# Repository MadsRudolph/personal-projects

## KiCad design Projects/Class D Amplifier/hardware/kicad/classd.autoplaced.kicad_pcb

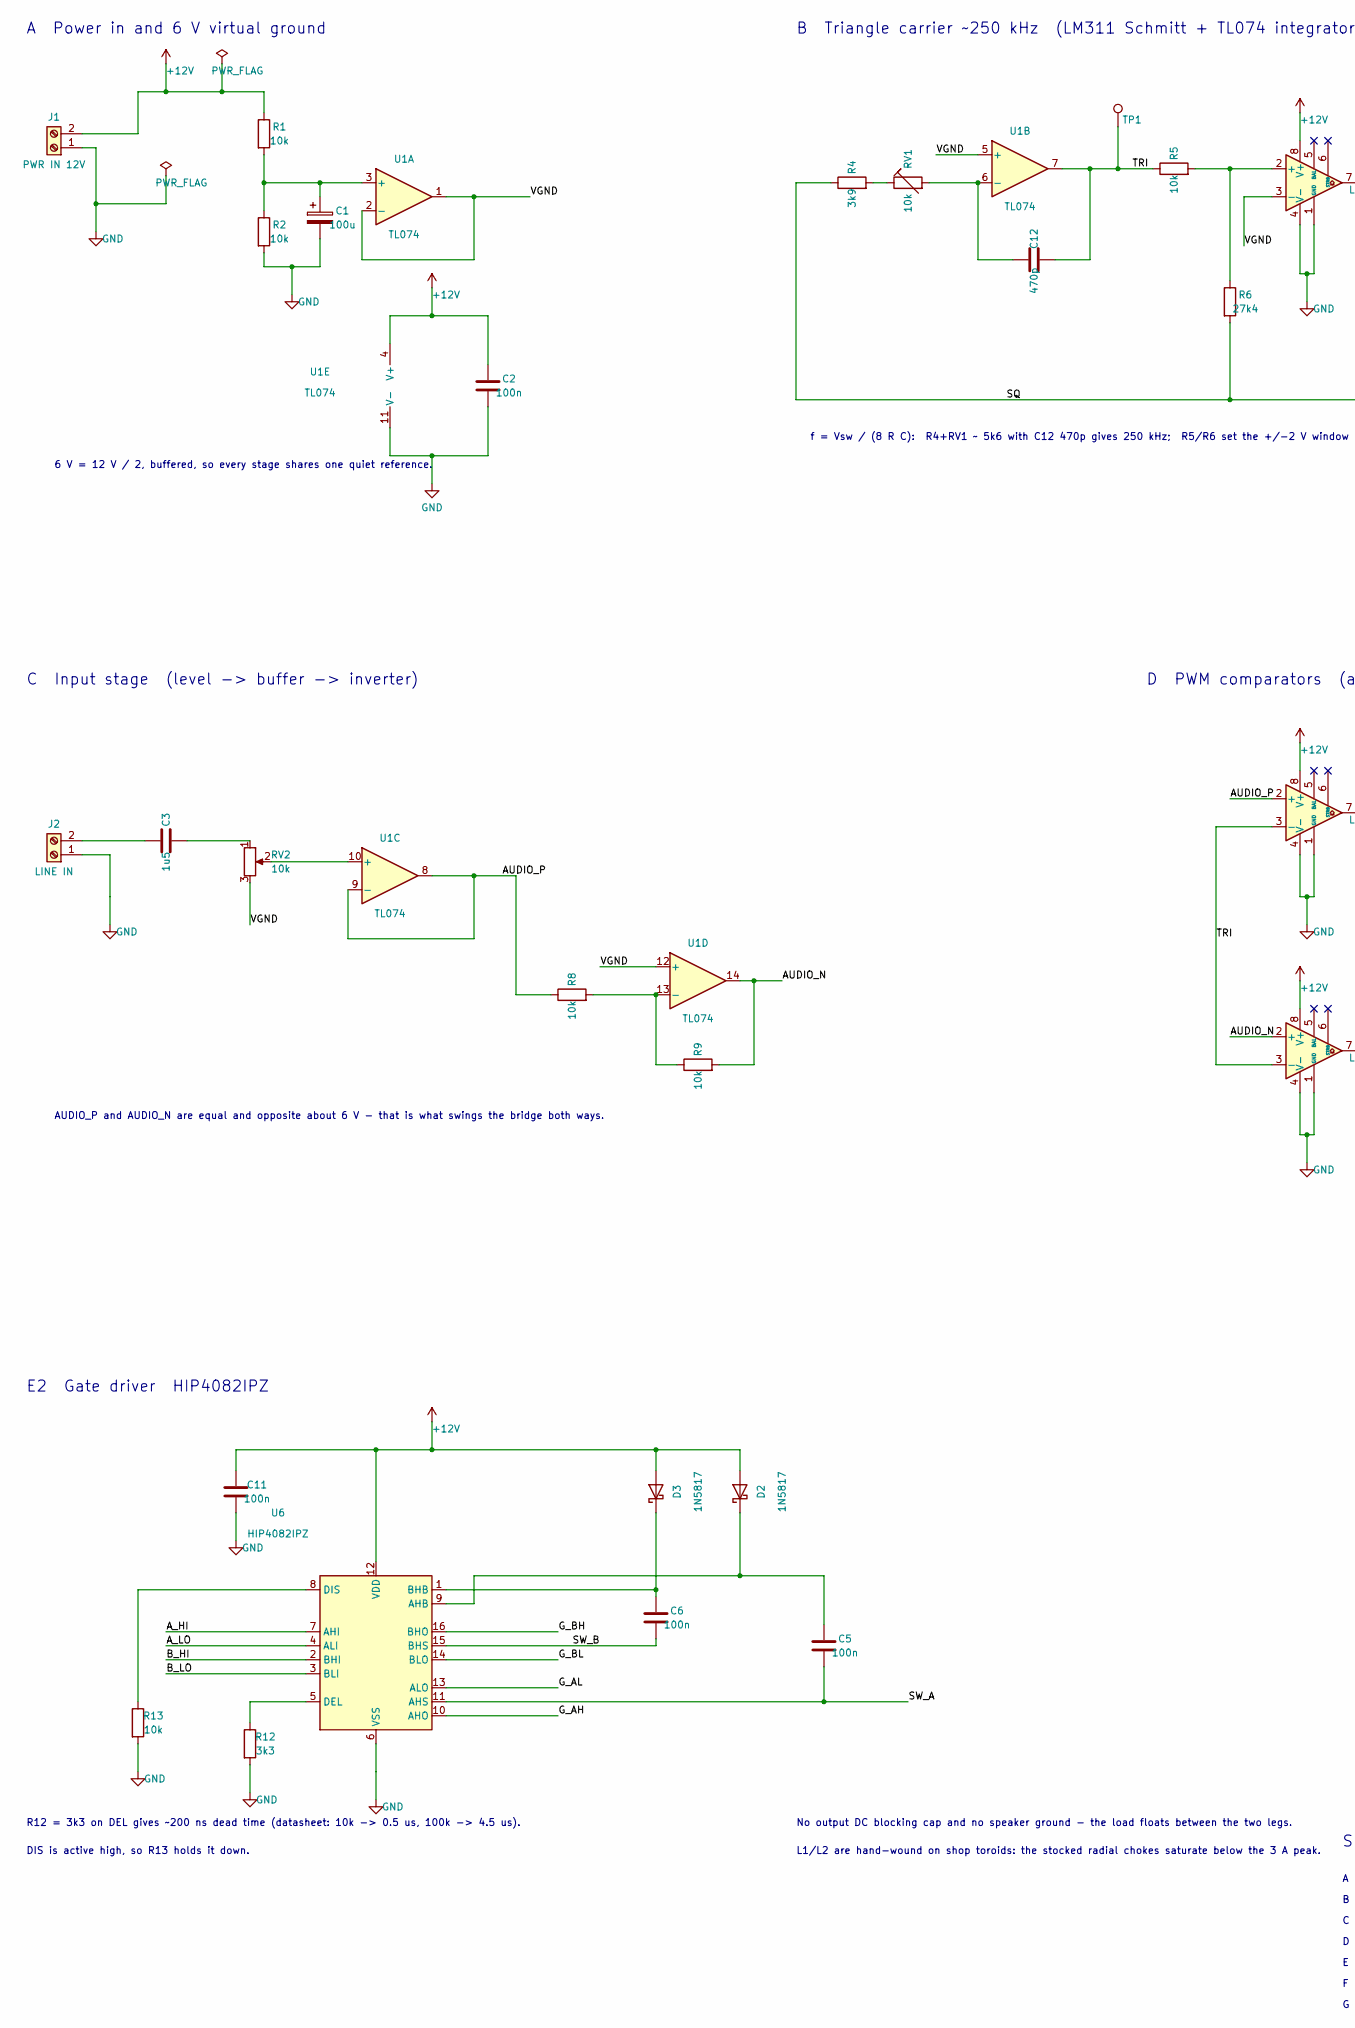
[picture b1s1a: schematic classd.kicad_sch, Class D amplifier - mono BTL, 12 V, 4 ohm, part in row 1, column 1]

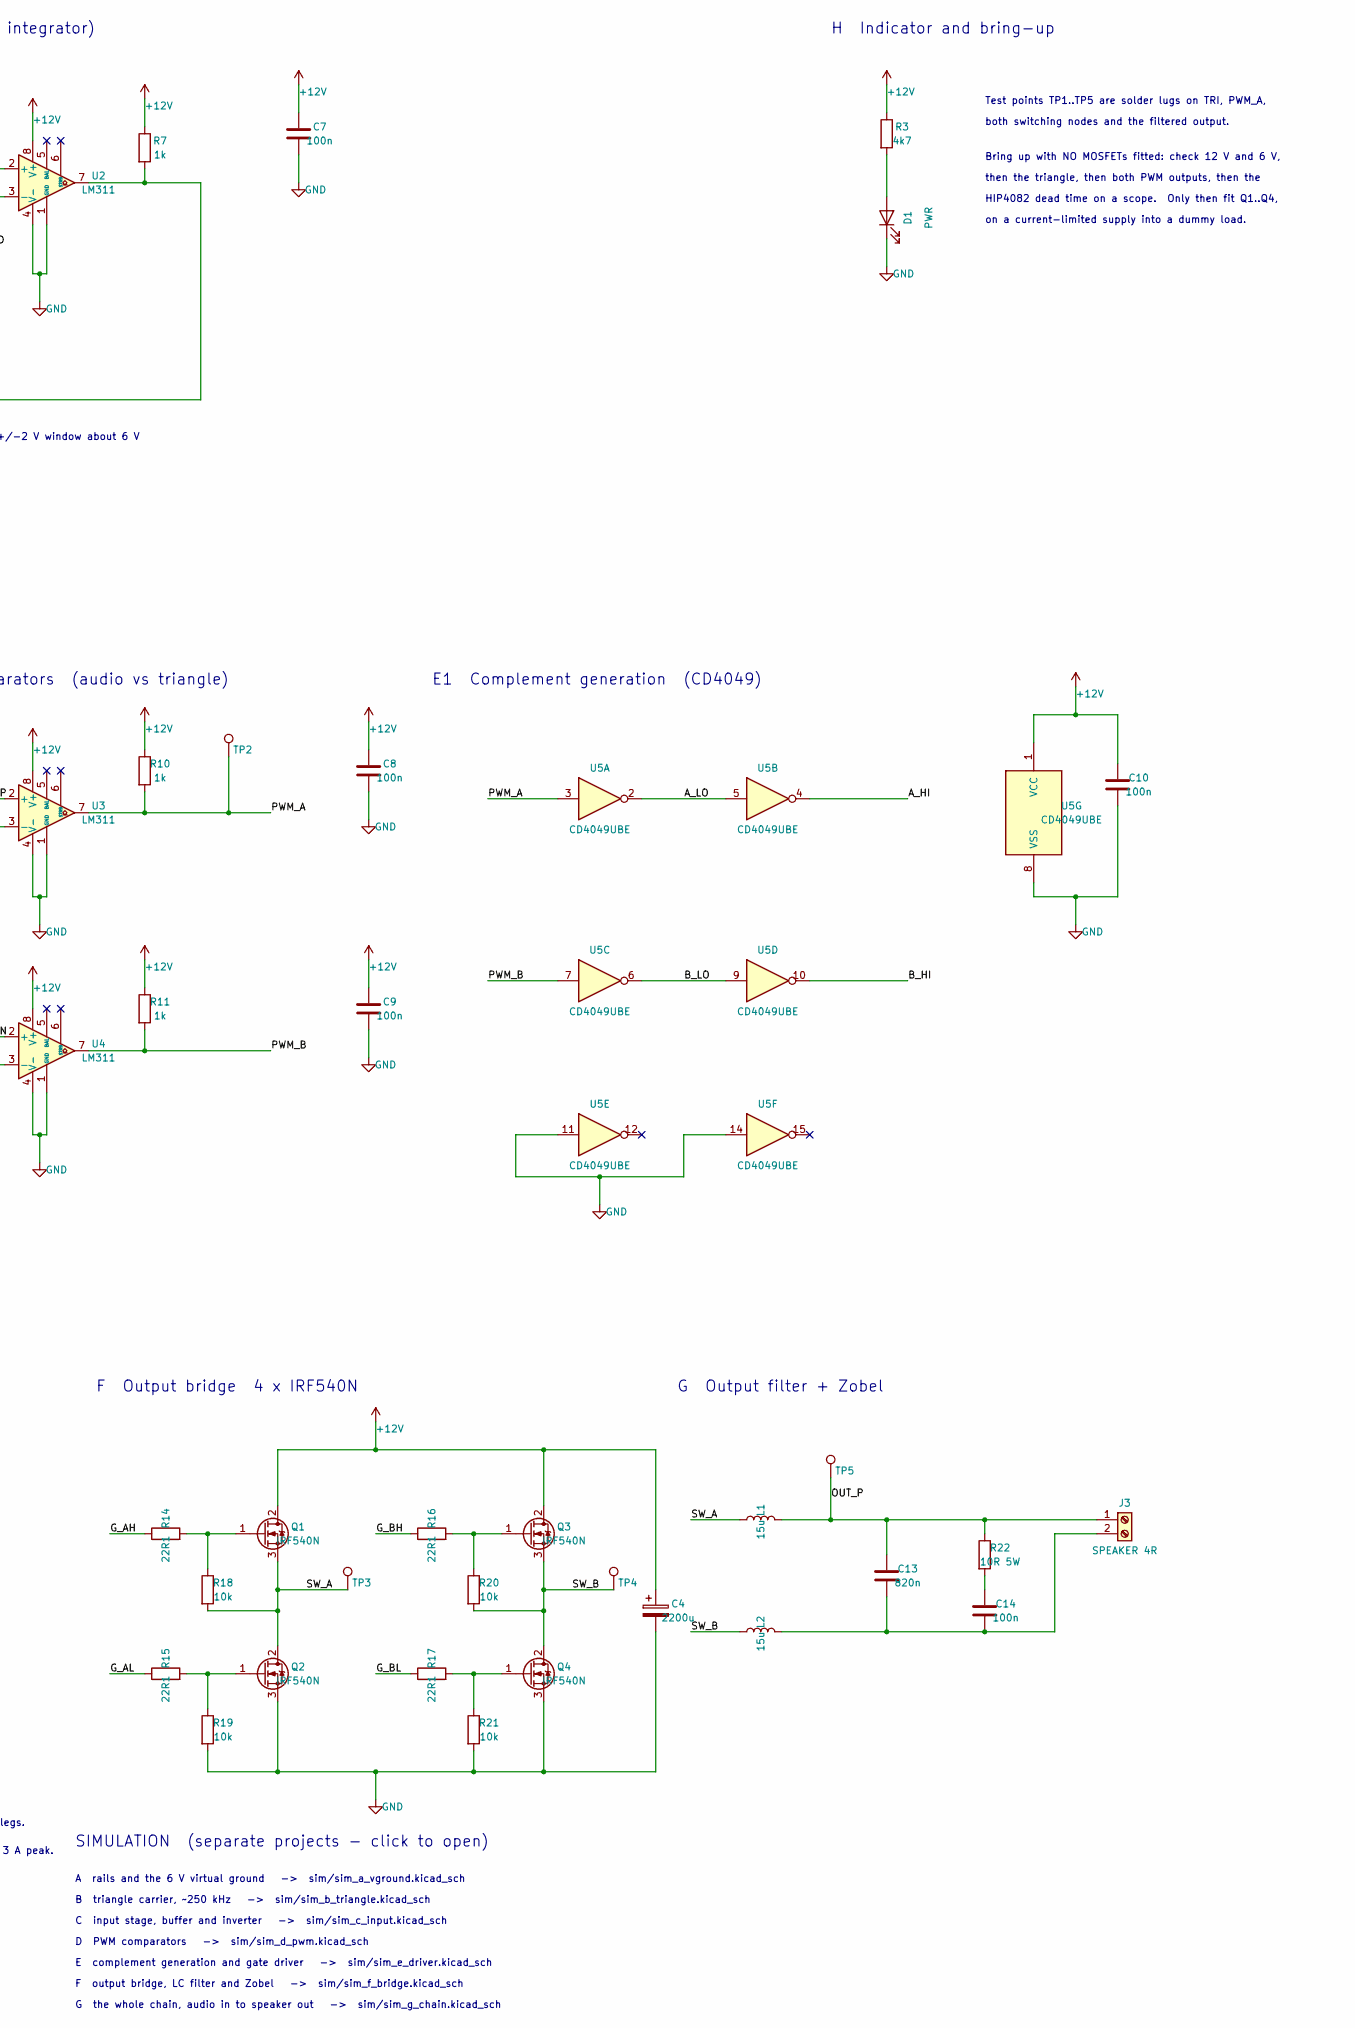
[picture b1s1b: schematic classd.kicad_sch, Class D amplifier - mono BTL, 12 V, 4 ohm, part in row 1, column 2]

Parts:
C1: 100u; CP_Radial_D8.0mm_P3.50mm
C2, C5, C6, C7, C8, C9, C10, C11: 100n; C_Disc_D5.0mm_W2.5mm_P5.00mm
C3: 1u5; C_Rect_L13.0mm_W5.0mm_P10.00mm_FKS3_FKP3_MKS4
C4: 2200u; CP_Radial_D18.0mm_P7.50mm
C12: 470p; C_Disc_D5.0mm_W2.5mm_P5.00mm
C13: 820n; C_Rect_L16.5mm_W5.0mm_P15.00mm_MKT
C14: 100n; C_Rect_L7.0mm_W3.5mm_P5.00mm
D1: PWR; LED_D3.0mm_P5.08mm_LaserPads
D2, D3: 1N5817; D_DO-41_SOD81_P10.16mm_Horizontal
J1: PWR IN 12V; TerminalBlock_bornier-2_P5.08mm
J2: LINE IN; TerminalBlock_bornier-2_P5.08mm
J3: SPEAKER 4R; TerminalBlock_bornier-2_P5.08mm
L1, L2: 15u; L_Toroid_Vertical_L34.5mm_W15.0mm_P28.20mm_LaserPads
Q1, Q2, Q3, Q4: IRF540N; TO-220-3_Vertical_LaserPads
R1, R2, R5, R8, R9, R13, R18, R19, R20, R21: 10k; R_Axial_DIN0207_L6.3mm_D2.5mm_P7.62mm_Horizontal
R3: 4k7; R_Axial_DIN0207_L6.3mm_D2.5mm_P7.62mm_Horizontal
R4: 3k9; R_Axial_DIN0207_L6.3mm_D2.5mm_P7.62mm_Horizontal
R6: 27k4; R_Axial_DIN0207_L6.3mm_D2.5mm_P7.62mm_Horizontal
R7, R10, R11: 1k; R_Axial_DIN0207_L6.3mm_D2.5mm_P7.62mm_Horizontal
R12: 3k3; R_Axial_DIN0207_L6.3mm_D2.5mm_P7.62mm_Horizontal
R14, R15, R16, R17: 22R1; R_Axial_DIN0207_L6.3mm_D2.5mm_P7.62mm_Horizontal
R22: 10R 5W; R_Axial_Power_L25.0mm_W9.0mm_P30.48mm
RV1: 10k; Potentiometer_Bourns_3296W_Vertical
RV2: 10k; Potentiometer_ACP_CA14V-15_Vertical
TP1, TP2, TP3, TP4, TP5: TestPoint_THTPad_2.5x2.5mm_Drill1.2mm
U1: TL074; DIP-14_W7.62mm_LongPads
U2, U3, U4: LM311; DIP-8_W7.62mm_LongPads
U5: CD4049UBE; DIP-16_W7.62mm_LongPads
U6: HIP4082IPZ; DIP-16_W7.62mm_LongPads

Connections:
/AUDIO_N: R9.2, U1.14, U4.2 (+)
/AUDIO_P: R8.1, U1.8, U1.9 (-), U3.2 (+)
/A_HI: U5.4, U6.7 (AHI)
/A_LO: U5.2, U5.5, U6.4 (ALI)
/B_HI: U5.10, U6.2 (BHI)
/B_LO: U5.6, U5.9, U6.3 (BLI)
/G_AH: R14.1, U6.10 (AHO)
/G_AL: R15.1, U6.13 (ALO)
/G_BH: R16.1, U6.16 (BHO)
/G_BL: R17.1, U6.14 (BLO)
/OUT_P: C13.1, J3.1, L1.2, R22.1, TP5.1 (1_1)
/PWM_A: R10.2, TP2.1 (1_1), U3.7, U5.3
/PWM_B: R11.2, U4.7, U5.7
/SQ: R4.1, R6.2, R7.2, U2.7
/SW_A: C5.2, L1.1, Q1.3 (S), Q2.2 (D), R18.2, TP3.1 (1_1), U6.11 (AHS)
/SW_B: C6.2, L2.1, Q3.3 (S), Q4.2 (D), R20.2, TP4.1 (1_1), U6.15 (BHS)
/TRI: C12.2, R5.1, TP1.1 (1_1), U1.7, U3.3 (-), U4.3 (-)
/VGND: RV2.3, U1.1, U1.2 (-), U1.5 (+), U1.12 (+), U2.3 (-)
unnamed: C3.2, RV2.1
unnamed: C14.1, R22.2
unnamed: D1.2 (A), R3.2
unnamed: C5.1, D2.1 (K), U6.9 (AHB)
unnamed: C6.1, D3.1 (K), U6.1 (BHB)
unnamed: C3.1, J2.2
unnamed: C13.2, C14.2, J3.2, L2.2
unnamed: Q1.1 (G), R14.2, R18.1
unnamed: Q2.1 (G), R15.2, R19.1
unnamed: Q3.1 (G), R16.2, R20.1
unnamed: Q4.1 (G), R17.2, R21.1
unnamed: R4.2, RV1.1
unnamed: C1.1, R1.2, R2.1, U1.3 (+)
unnamed: C12.1, RV1.2, U1.6 (-)
unnamed: RV2.2, U1.10 (+)
unnamed: R8.2, R9.1, U1.13 (-)
unnamed: R5.2, R6.1, U2.2 (+)
unnamed: R12.1, U6.5 (DEL)
unnamed: R13.1, U6.8 (DIS)

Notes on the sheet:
A Power in and 6 V virtual ground
6 V = 12 V / 2, buffered, so every stage shares one quiet reference.
B Triangle carrier ~250 kHz (LM311 Schmitt + TL074 integrator)
f = Vsw / (8 R C): R4+RV1 ~ 5k6 with C12 470p gives 250 kHz; R5/R6 set the +/-2 V window about 6 V
H Indicator and bring-up
Test points TP1..TP5 are solder lugs on TRI, PWM_A,
both switching nodes and the filtered output.
Bring up with NO MOSFETs fitted: check 12 V and 6 V,
then the triangle, then both PWM outputs, then the
HIP4082 dead time on a scope. Only then fit Q1..Q4,
on a current-limited supply into a dummy load.
C Input stage (level -> buffer -> inverter)
AUDIO_P and AUDIO_N are equal and opposite about 6 V - that is what swings the bridge both ways.
D PWM comparators (audio vs triangle)
E1 Complement generation (CD4049)
E2 Gate driver HIP4082IPZ
R12 = 3k3 on DEL gives ~200 ns dead time (datasheet: 10k -> 0.5 us, 100k -> 4.5 us).
DIS is active high, so R13 holds it down.
F Output bridge 4 x IRF540N
G Output filter + Zobel
No output DC blocking cap and no speaker ground - the load floats between the two legs.
L1/L2 are hand-wound on shop toroids: the stocked radial chokes saturate below the 3 A peak.
SIMULATION (separate projects - click to open)
A rails and the 6 V virtual ground -> sim/sim_a_vground.kicad_sch
B triangle carrier, ~250 kHz -> sim/sim_b_triangle.kicad_sch
C input stage, buffer and inverter -> sim/sim_c_input.kicad_sch
D PWM comparators -> sim/sim_d_pwm.kicad_sch
E complement generation and gate driver -> sim/sim_e_driver.kicad_sch
F output bridge, LC filter and Zobel -> sim/sim_f_bridge.kicad_sch
G the whole chain, audio in to speaker out -> sim/sim_g_chain.kicad_sch

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
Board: 2 copper layers, 61 parts (0 on the bottom side), 39 nets, no tracks yet.

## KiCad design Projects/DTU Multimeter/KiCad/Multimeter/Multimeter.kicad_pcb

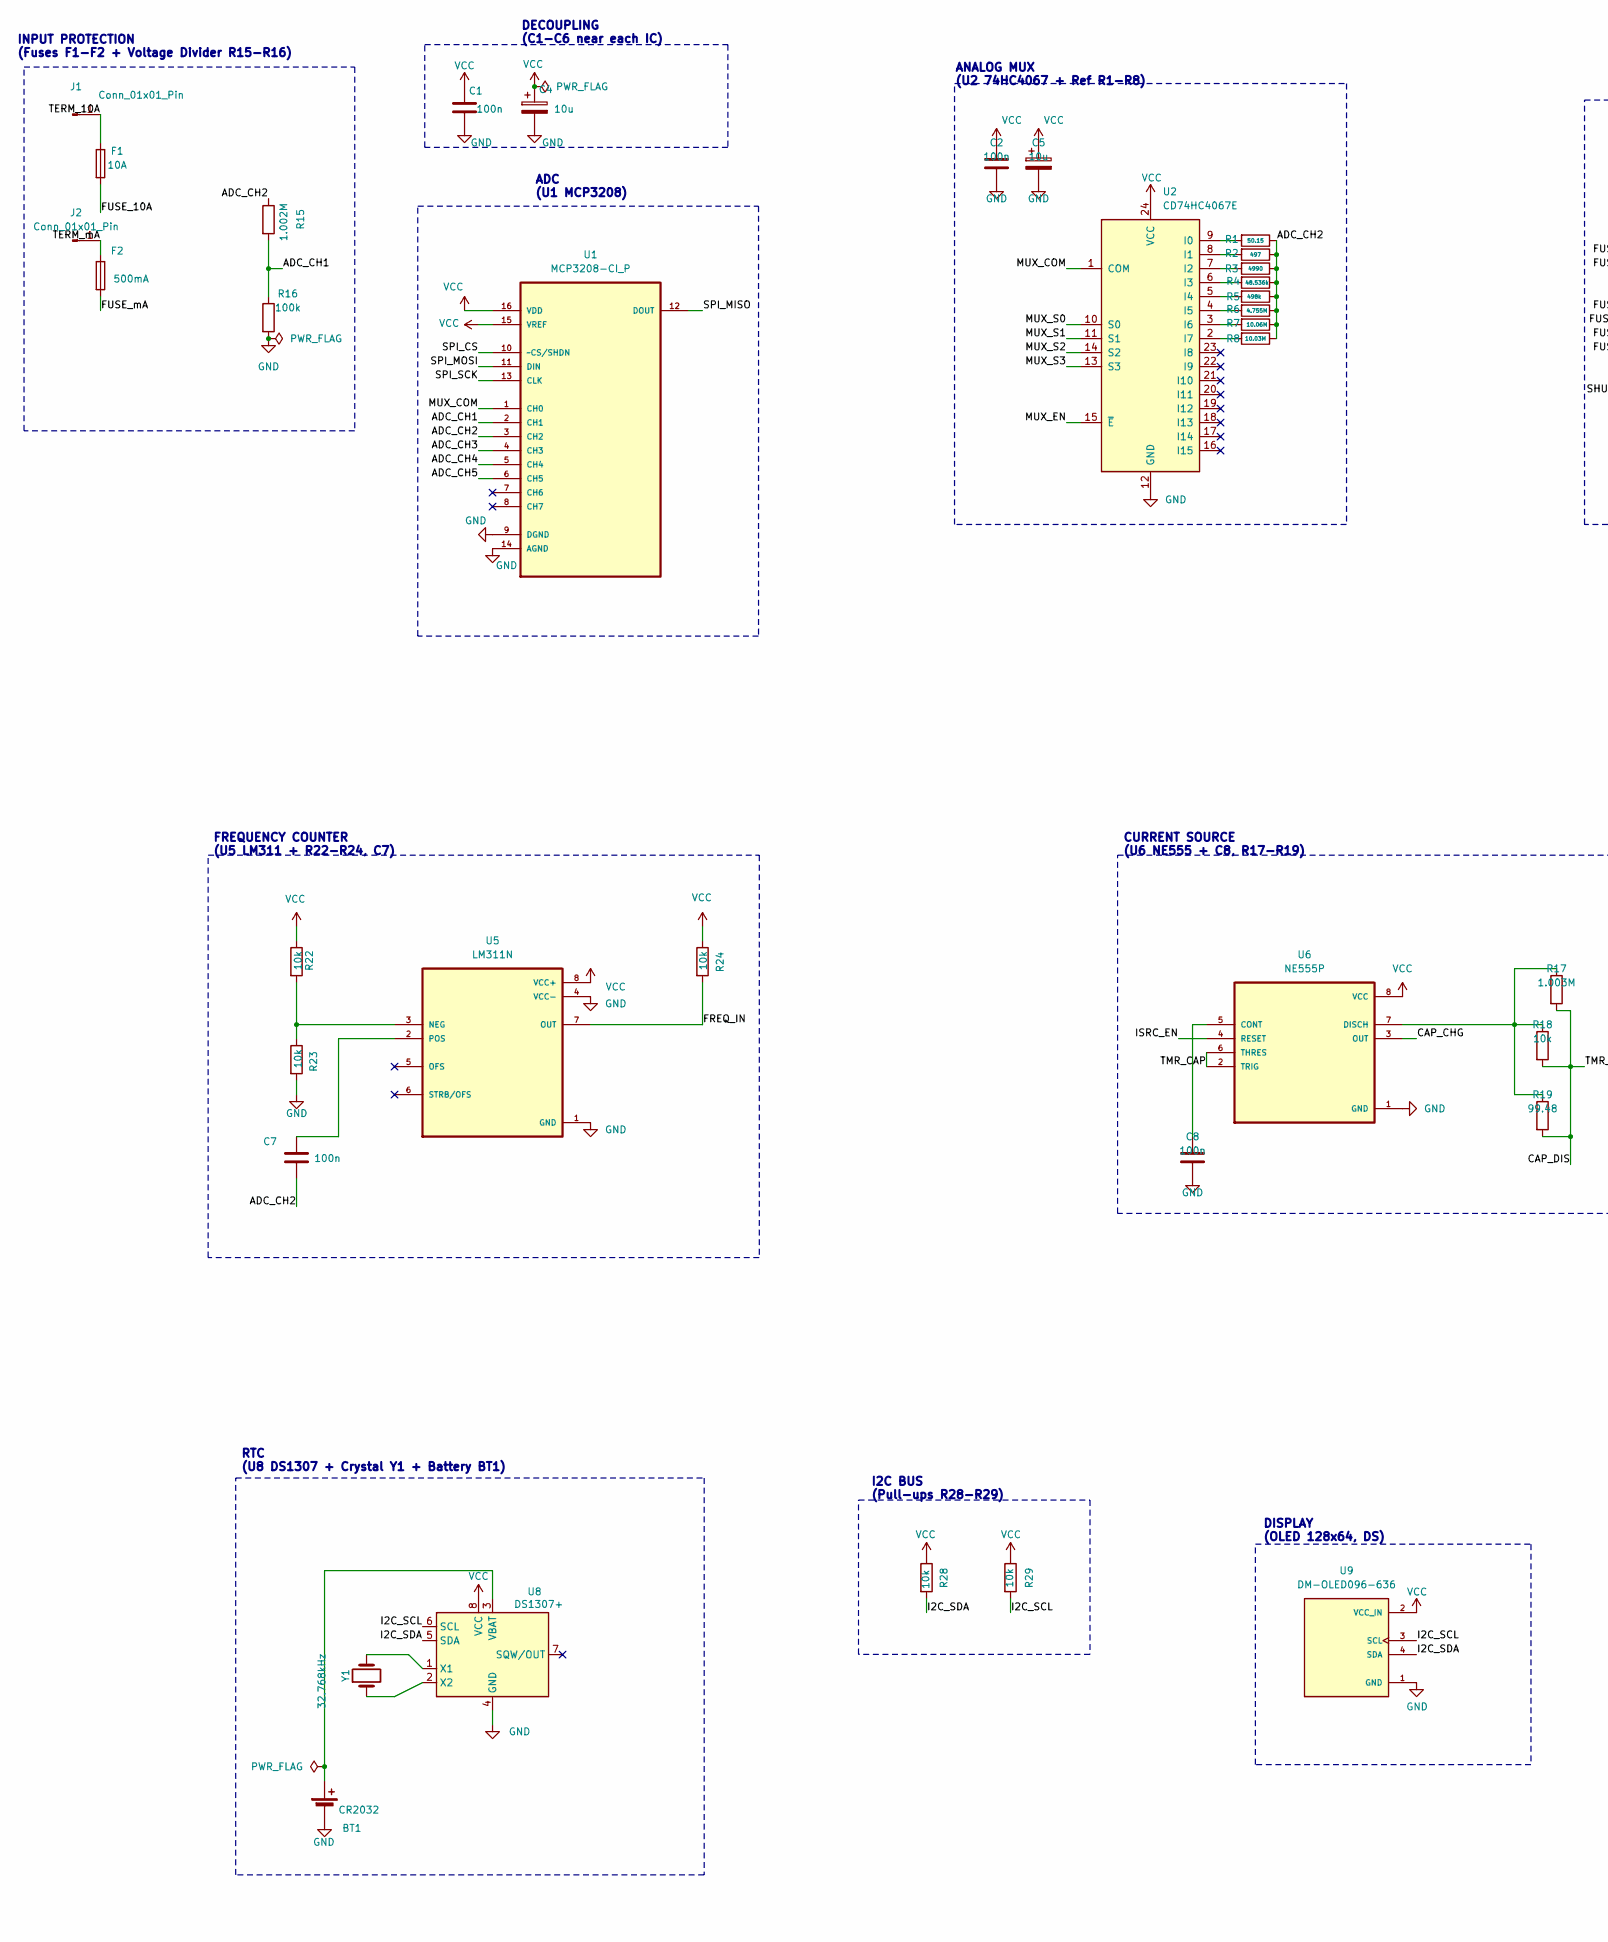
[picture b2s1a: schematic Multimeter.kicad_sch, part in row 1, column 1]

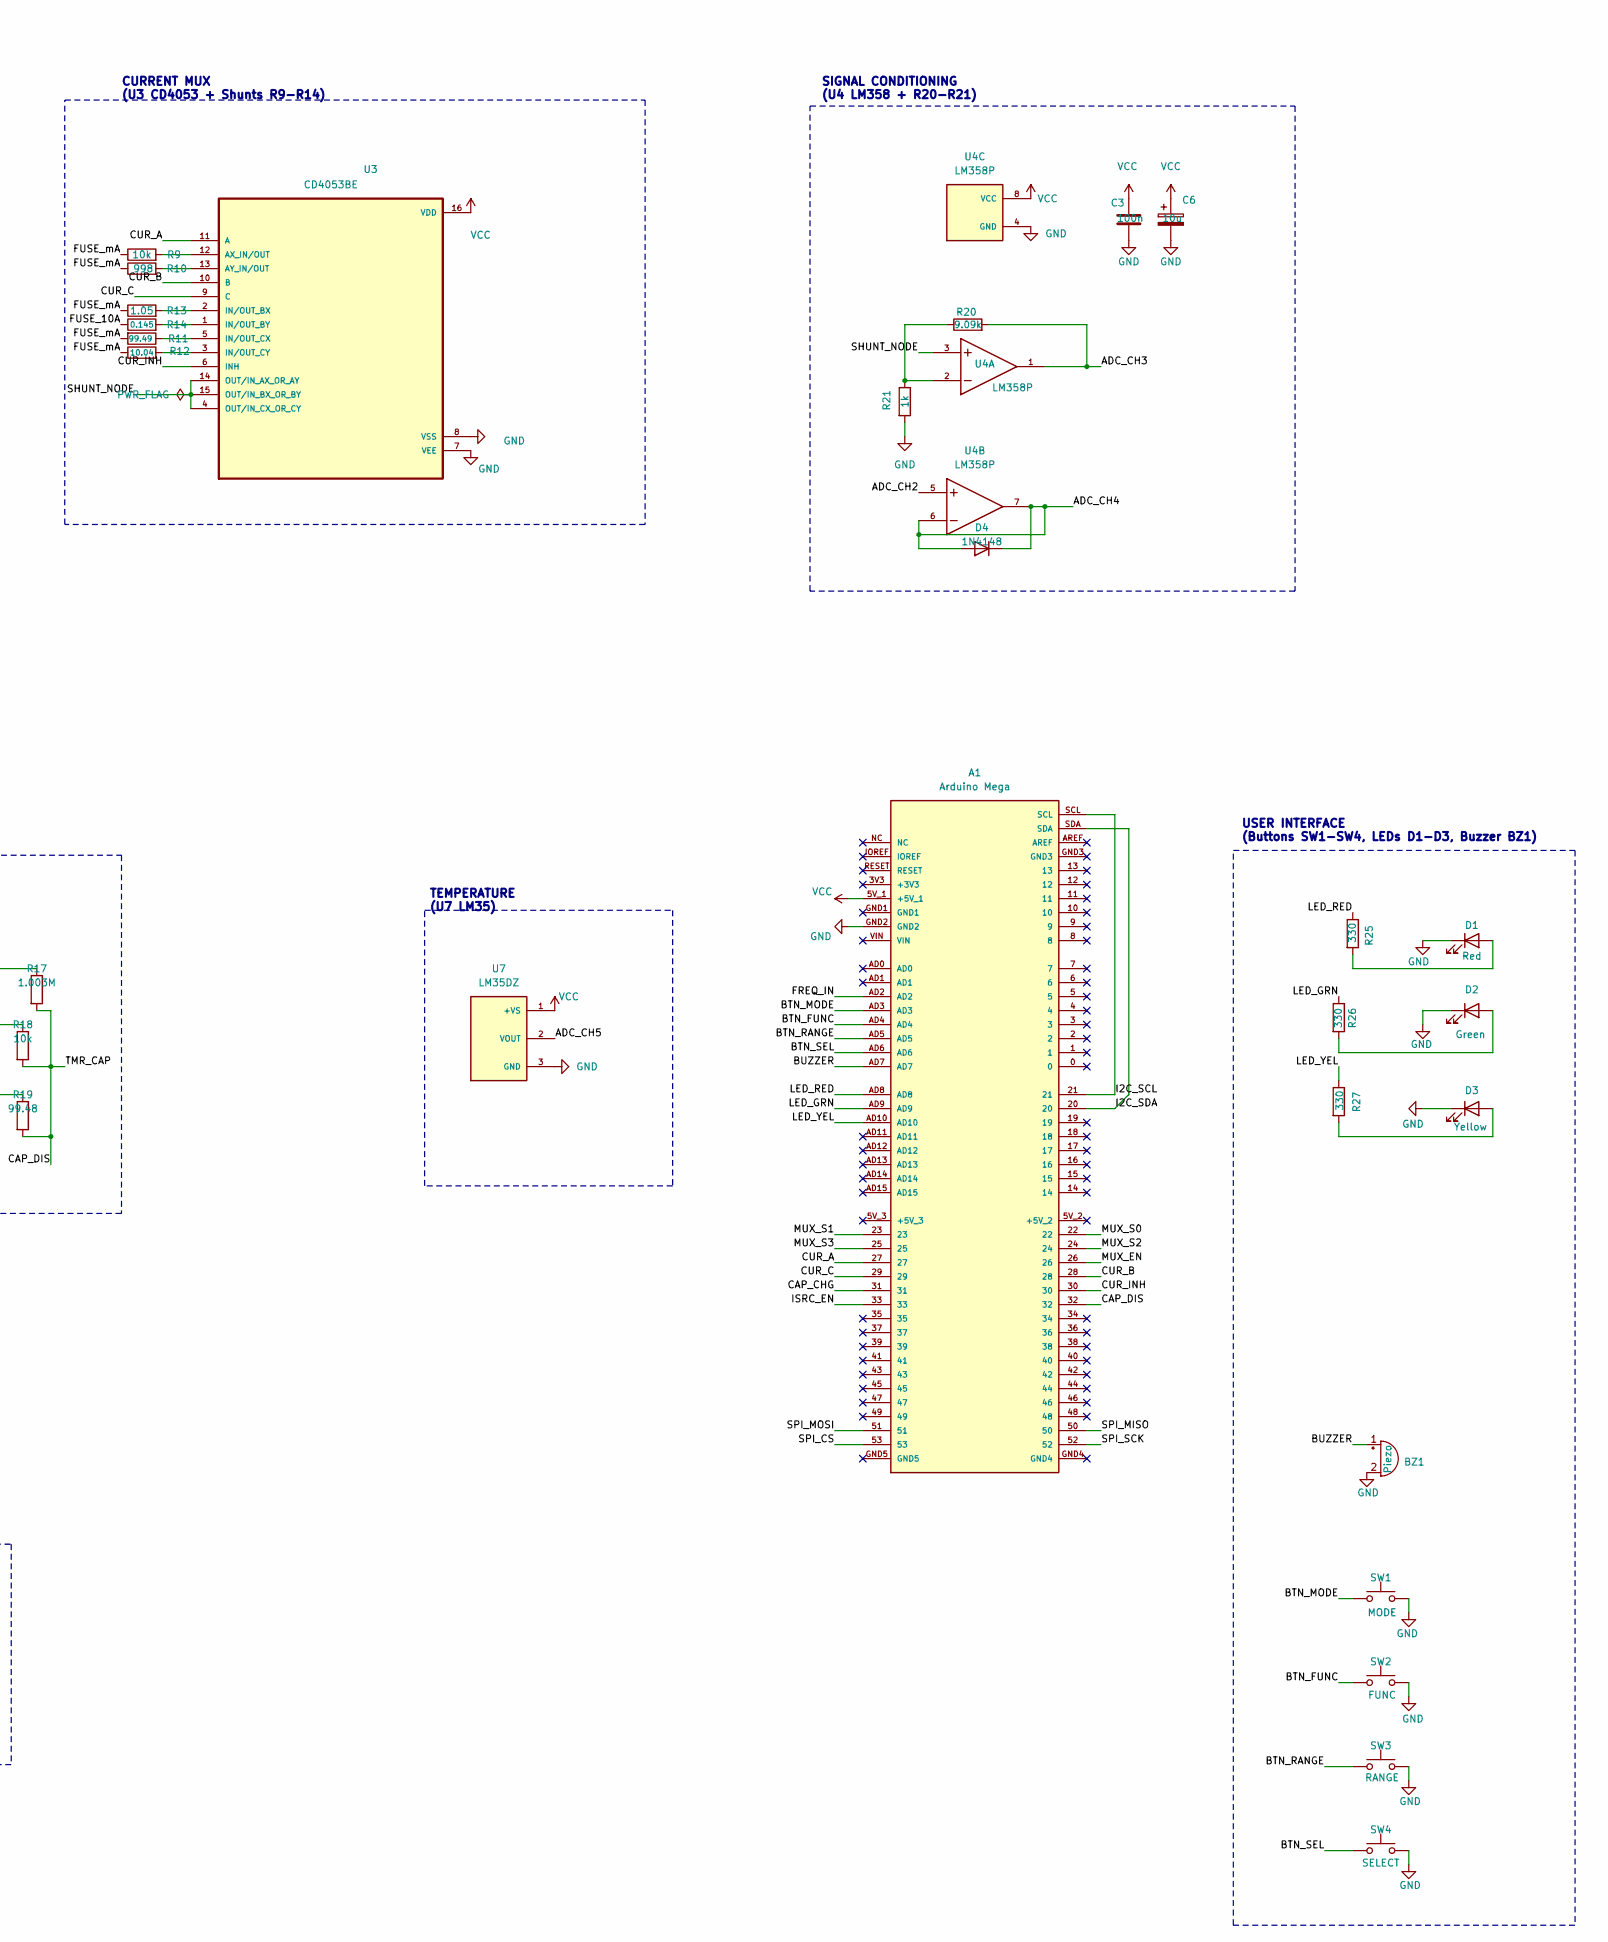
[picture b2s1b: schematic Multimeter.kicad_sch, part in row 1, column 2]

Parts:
A1: Arduino Mega; MODULE_A000067; PARTREV 3
BT1: CR2032; BatteryHolder_Keystone_3034_1x20mm
BZ1: Piezo; Buzzer_12x9.5RM7.6
C1, C2, C3, C7, C8: 100n; C_Disc_D5.0mm_W2.5mm_P2.50mm
C4, C5, C6: 10u; CP_Radial_D5.0mm_P2.50mm
D1: Red; LED_D3.0mm
D2: Green; LED_D3.0mm
D3: Yellow; LED_D3.0mm
D4: 1N4148; D_DO-35_SOD27_P7.62mm_Horizontal
F1: 10A; Fuseholder_Cylinder-5x20mm_Schurter_0031_8201_Horizontal_Op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
F2: 500mA; Fuseholder_Cylinder-5x20mm_Schurter_0031_8201_Horizontal_Op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
J1, J2: Conn_01x01_Pin; Banana_Jack_1Pin
R1: 50.15; R_Axial_DIN0207_L6.3mm_D2.5mm_P10.16mm_Horizontal
R2: 497; R_Axial_DIN0207_L6.3mm_D2.5mm_P10.16mm_Horizontal
R3: 4990; R_Axial_DIN0207_L6.3mm_D2.5mm_P10.16mm_Horizontal
R4: 48.536k; R_Axial_DIN0207_L6.3mm_D2.5mm_P10.16mm_Horizontal
R5: 498k; R_Axial_DIN0207_L6.3mm_D2.5mm_P10.16mm_Horizontal
R6: 4.755M; R_Axial_DIN0207_L6.3mm_D2.5mm_P10.16mm_Horizontal
R7: 10.06M; R_Axial_DIN0207_L6.3mm_D2.5mm_P10.16mm_Horizontal
R8: 10.03M; R_Axial_DIN0207_L6.3mm_D2.5mm_P10.16mm_Horizontal
R9, R18, R22, R23, R24, R28, R29: 10k; R_Axial_DIN0207_L6.3mm_D2.5mm_P10.16mm_Horizontal
R10: 998; R_Axial_DIN0207_L6.3mm_D2.5mm_P10.16mm_Horizontal
R11: 99.49; R_Axial_DIN0207_L6.3mm_D2.5mm_P10.16mm_Horizontal
R12: 10.04; R_Axial_DIN0207_L6.3mm_D2.5mm_P10.16mm_Horizontal
R13: 1.05; R_Axial_DIN0207_L6.3mm_D2.5mm_P10.16mm_Horizontal
R14: 0.145; R_Axial_DIN0207_L6.3mm_D2.5mm_P10.16mm_Horizontal
R15: 1.002M; R_Axial_DIN0207_L6.3mm_D2.5mm_P10.16mm_Horizontal
R16: 100k; R_Axial_DIN0207_L6.3mm_D2.5mm_P10.16mm_Horizontal
R17: 1.003M; R_Axial_DIN0207_L6.3mm_D2.5mm_P10.16mm_Horizontal
R19: 99.48; R_Axial_DIN0207_L6.3mm_D2.5mm_P10.16mm_Horizontal
R20: 9.09k; R_Axial_DIN0207_L6.3mm_D2.5mm_P10.16mm_Horizontal
R21: 1k; R_Axial_DIN0207_L6.3mm_D2.5mm_P10.16mm_Horizontal
R25, R26, R27: 330; R_Axial_DIN0207_L6.3mm_D2.5mm_P10.16mm_Horizontal
SW1: MODE; SW_PUSH_6mm
SW2: FUNC; SW_PUSH_6mm
SW3: RANGE; SW_PUSH_6mm
SW4: SELECT; SW_PUSH_6mm
U1: MCP3208-CI_P; DIP254P762X432-16; MPN MCP3208-CI/P
U2: CD74HC4067E; DIP-24_18.0mmx34.29mm_W15.24mm
U3: CD4053BE; DIP794W45P254L1969H508Q16
U4: LM358P; DIP794W45P254L959H508Q8; PARTREV FEBRUARY 2021
U5: LM311N; DIP794W45P254L959H508Q8
U6: NE555P; DIP794W45P254L959H508Q8
U7: LM35DZ; IC_LM35DZ; PARTREV H
U8: DS1307+; DIP-8_W7.62mm
U9: DM-OLED096-636; MODULE_DM-OLED096-636; PARTREV 2018-09-10
Y1: 32.768kHz; Crystal_C38-LF_D3.0mm_L8.0mm_Horizontal

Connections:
/ADC_CH1: R15.2, R16.1, U1.2 (CH1)
/ADC_CH2: C7.2, R1.1, R2.1, R3.1, R4.1, R5.1, R6.1, R7.1, R8.1, R15.1, U1.3 (CH2), U4.5
/ADC_CH3: R20.2, U1.4 (CH3), U4.1
/ADC_CH4: D4.1 (K), D4.2 (A), U1.5 (CH4), U4.6, U4.7
/ADC_CH5: U1.6 (CH5), U7.2 (VOUT)
/BTN_FUNC: A1.AD4, SW2.1
/BTN_MODE: A1.AD3, SW1.1
/BTN_RANGE: A1.AD5, SW3.1
/BTN_SEL: A1.AD6, SW4.1
/BUZZER: A1.AD7, BZ1.1 (+)
/CAP_CHG: A1.31, U6.3 (OUT)
/CAP_DIS: A1.32, R17.2, R18.2, R19.2, U6.2 (TRIG), U6.6 (THRES)
/CUR_A: A1.27, U3.11 (A)
/CUR_B: A1.28, U3.10 (B)
/CUR_C: A1.29, U3.9 (C)
/CUR_INH: A1.30, U3.6 (INH)
/FREQ_IN: A1.AD2, R24.2, U5.7 (OUT)
/FUSE_10A: F1.2, R14.1
/FUSE_mA: F2.2, R9.1, R10.1, R11.2, R12.1, R13.1
/I2C_SCL: A1.21, A1.SCL, R29.2, U8.6 (SCL), U9.3 (SCL)
/I2C_SDA: A1.20, A1.SDA, R28.2, U8.5 (SDA), U9.4 (SDA)
/ISRC_EN: A1.33, U6.4 (RESET)
/LED_GRN: A1.AD9, R26.1
/LED_RED: A1.AD8, R25.1
/LED_YEL: A1.AD10, R27.1
/MUX_COM: U1.1 (CH0), U2.1 (COM)
/MUX_EN: A1.26, U2.15 (~E)
/MUX_S0: A1.22, U2.10 (S0)
/MUX_S1: A1.23, U2.11 (S1)
/MUX_S2: A1.24, U2.14 (S2)
/MUX_S3: A1.25, U2.13 (S3)
/SHUNT_NODE: U3.4 (OUT/IN_CX_OR_CY), U3.14 (OUT/IN_AX_OR_AY), U3.15 (OUT/IN_BX_OR_BY), U4.3
/SPI_CS: A1.53, U1.10 (~CS/SHDN)
/SPI_MISO: A1.50, U1.12 (DOUT)
/SPI_MOSI: A1.51, U1.11 (DIN)
/SPI_SCK: A1.52, U1.13 (CLK)
/TERM_10A: F1.1, J1.1
/TERM_mA: F2.1, J2.1
GND: A1.GND2, BT1.2 (-), BZ1.2 (-), C1.2, C2.2, C3.2, C4.2, C5.2, C6.2, C8.2, D1.1 (K), D2.1 (K), D3.1 (K), R16.2, R21.2, R23.2, SW1.2, SW2.2, SW3.2, SW4.2, U1.9 (DGND), U1.14 (AGND), U2.12 (GND), U3.7 (VEE), U3.8 (VSS), U4.4 (GND), U5.1 (GND), U5.4 (VCC-), U6.1 (GND), U7.3 (GND), U8.4 (GND), U9.1 (GND)
unnamed: BT1.1 (+), U8.3 (VBAT)
unnamed: D1.2 (A), R25.2
unnamed: D2.2 (A), R26.2
unnamed: D3.2 (A), R27.2
unnamed: R20.1, R21.1, U4.2
unnamed: R1.2, U2.9 (I0)
unnamed: R2.2, U2.8 (I1)
unnamed: R3.2, U2.7 (I2)
unnamed: R4.2, U2.6 (I3)
unnamed: R5.2, U2.5 (I4)
unnamed: R6.2, U2.4 (I5)
unnamed: R7.2, U2.3 (I6)
unnamed: R8.2, U2.2 (I7)
unnamed: R9.2, U3.12 (AX_IN/OUT)
unnamed: R10.2, U3.13 (AY_IN/OUT)
unnamed: R13.2, U3.2 (IN/OUT_BX)
unnamed: R14.2, U3.1 (IN/OUT_BY)
unnamed: R11.1, U3.5 (IN/OUT_CX)
unnamed: R12.2, U3.3 (IN/OUT_CY)
unnamed: R22.2, R23.1, U5.3 (NEG)
unnamed: C7.1, U5.2 (POS)
unnamed: C8.1, U6.5 (CONT)
unnamed: R17.1, R18.1, R19.1, U6.7 (DISCH)
unnamed: U8.1 (X1), Y1.2
unnamed: U8.2 (X2), Y1.1
VCC: A1.5V_1 (+5V_1), C1.1, C2.1, C3.1, C4.1, C5.1, C6.1, R22.1, R24.1, R28.1, R29.1, U1.15 (VREF), U1.16 (VDD), U2.24 (VCC), U3.16 (VDD), U4.8 (VCC), U5.8 (VCC+), U6.8 (VCC), U7.1 (+VS), U8.8 (VCC), U9.2 (VCC_IN)

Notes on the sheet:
FREQUENCY COUNTER (U5 LM311 + R22-R24, C7)
CURRENT SOURCE (U6 NE555 + C8, R17-R19)
RTC (U8 DS1307 + Crystal Y1 + Battery BT1)
ADC (U1 MCP3208)
INPUT PROTECTION (Fuses F1-F2 + Voltage Divider R15-R16)
USER INTERFACE (Buttons SW1-SW4, LEDs D1-D3, Buzzer BZ1)
I2C BUS (Pull-ups R28-R29)
SIGNAL CONDITIONING (U4 LM358 + R20-R21)
DECOUPLING (C1-C6 near each IC)
TEMPERATURE (U7 LM35)
ANALOG MUX (U2 74HC4067 + Ref R1-R8)
CURRENT MUX (U3 CD4053 + Shunts R9-R14)
DISPLAY (OLED 128x64, DS)

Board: 2 copper layers, 62 parts (0 on the bottom side), 65 nets, no tracks yet.

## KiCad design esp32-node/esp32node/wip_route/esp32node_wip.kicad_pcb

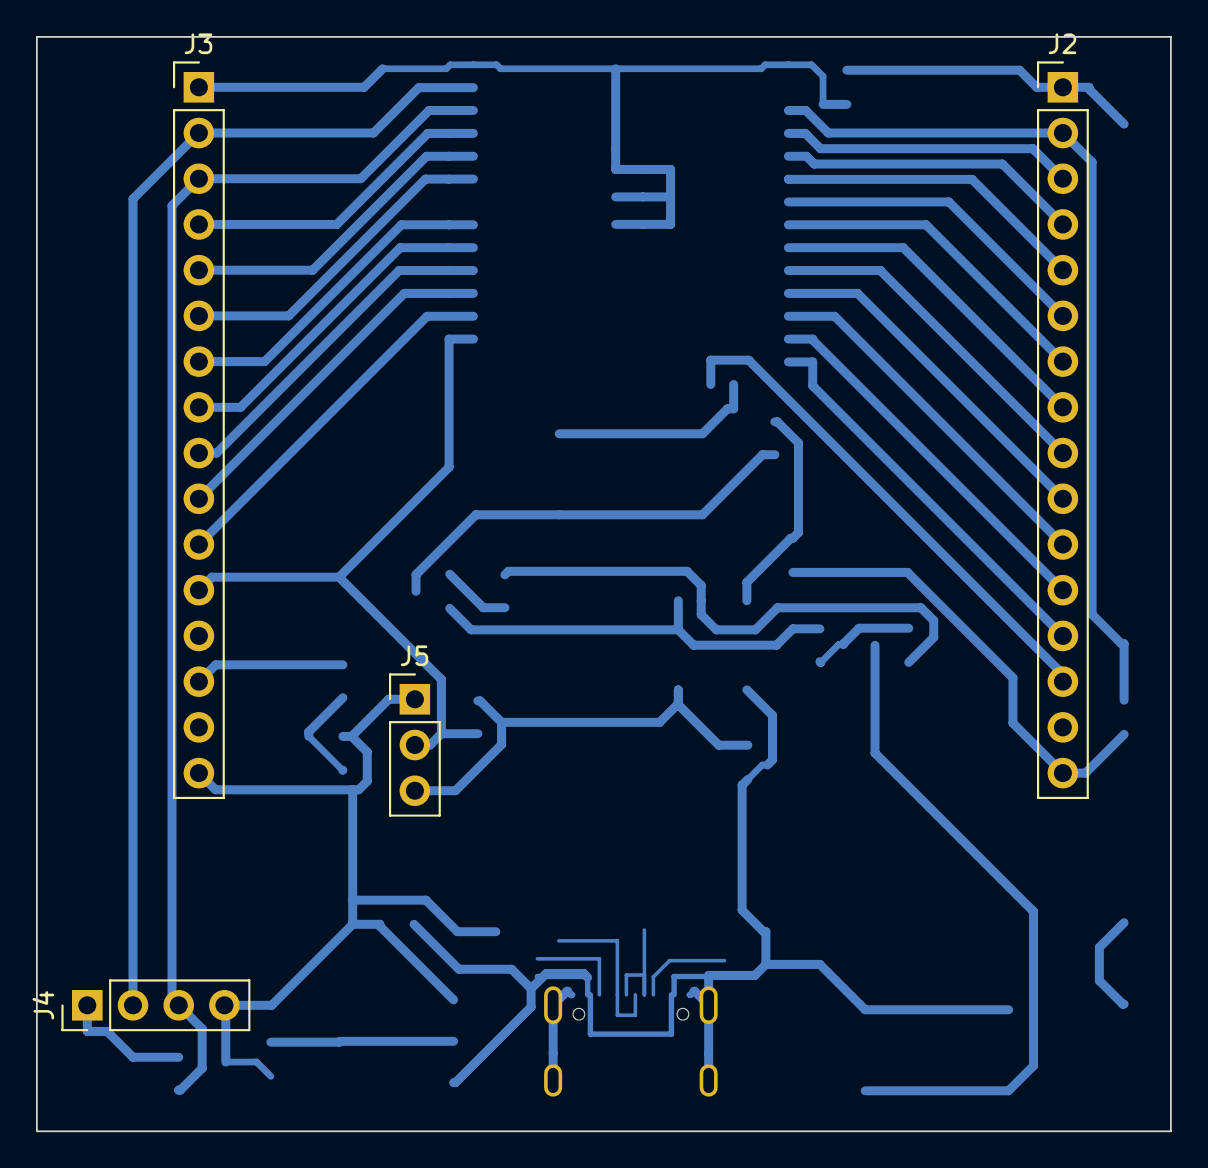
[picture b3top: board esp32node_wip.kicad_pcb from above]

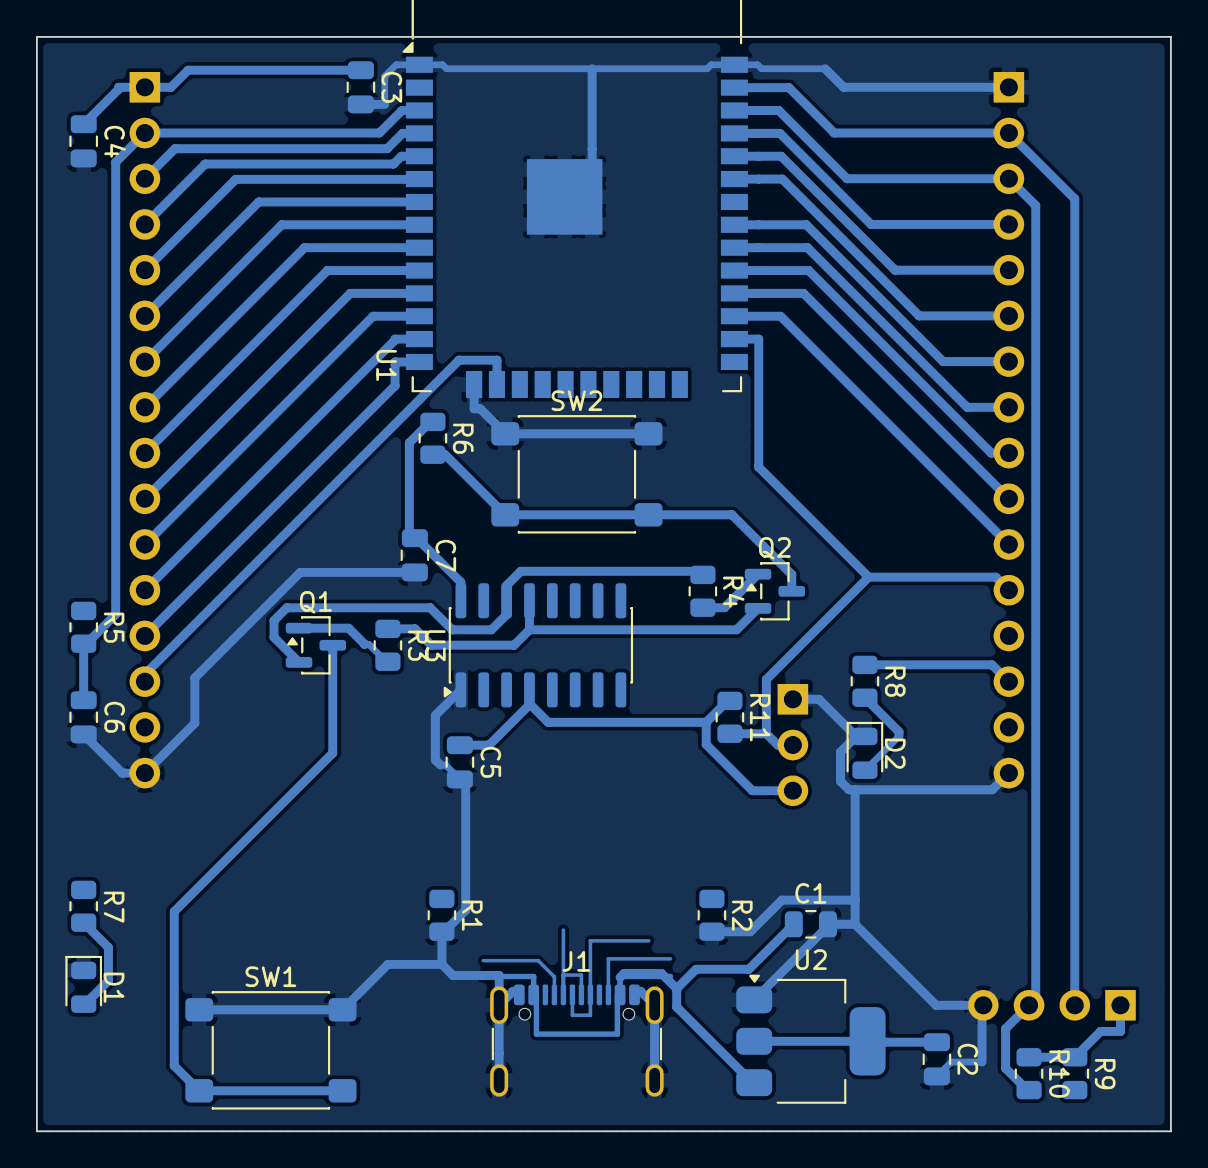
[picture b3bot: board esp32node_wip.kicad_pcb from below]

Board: 2 copper layers, 63.0 x 60.8 mm, 32 parts (28 on the bottom side), 40 nets.

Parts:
C1, C2, C4: 10u; C_0805_2012Metric
C3, C5, C7: 100n; C_0805_2012Metric
C6: 1u; C_0805_2012Metric
D1: LED red (power); LED_0805_2012Metric
D2: LED blue; LED_0805_2012Metric
J1: USB-C; USB_C_Receptacle_GCT_USB4105-xx-A_16P_TopMnt_Horizontal
J2: GPIO L; PinHeader_1x16_P2.54mm_Vertical
J3: GPIO R; PinHeader_1x16_P2.54mm_Vertical
J4: I2C; PinHeader_1x04_P2.54mm_Vertical
J5: 1-Wire; PinHeader_1x03_P2.54mm_Vertical
Q1, Q2: S8050; SOT-23
R1, R2: 5.1k; R_0805_2012Metric
R3, R4, R5, R6: 10k; R_0805_2012Metric
R7, R8: 1k; R_0805_2012Metric
R9, R10, R11: 4.7k; R_0805_2012Metric
SW1: RESET; SW_SPST_PTS645Sx43SMTR92
SW2: BOOT; SW_SPST_PTS645Sx43SMTR92
U1: ESP32-WROOM-32; ESP32-WROOM-32_NoVias
U2: AMS1117-3.3; SOT-223-3_TabPin2
U3: CH340C; SOIC-16_3.9x9.9mm_P1.27mm

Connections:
+3V3: C2.1, C3.1, C4.1, C5.1, C7.1, J2.1, J4.1, J5.3, R5.1, R6.1, R7.1, R9.1, R10.1, R11.1, U1.2, U2.2, U3.4, U3.16
+5V: C1.1, J1.A4, J1.A9, J1.B4, J1.B9, J2.15, U2.3
/DTR: Q2.2, R3.1, U3.13
/EN: C6.1, J2.2, Q1.3, R5.2, SW1.2, U1.3
/IO0: J3.13, Q2.3, R6.2, SW2.2, U1.25
/IO2: J3.14, R8.1, U1.24
/IO4: J3.12, J5.2, R11.2, U1.26
/IO5: J3.9, U1.29
/IO12: J2.13, U1.14
/IO13: J2.14, U1.16
/IO14: J2.12, U1.13
/IO15: J3.15, U1.23
/IO16: J3.11, U1.27
/IO17: J3.10, U1.28
/IO18: J3.8, U1.30
/IO19: J3.7, U1.31
/IO21: J3.6, U1.33
/IO22: J3.3, J4.3, R10.2, U1.36
/IO23: J3.2, J4.2, R9.2, U1.37
/IO25: J2.9, U1.10
/IO26: J2.10, U1.11
/IO27: J2.11, U1.12
/IO32: J2.7, U1.8
/IO33: J2.8, U1.9
/IO34: J2.5, U1.6
/IO35: J2.6, U1.7
/RTS: Q1.2, R4.1, U3.14
/RXD0: J3.5, U1.34, U3.2
/SVN: J2.4, U1.5
/SVP: J2.3, U1.4
/TXD0: J3.4, U1.35, U3.3
/USB_D+: J1.A6, J1.B6, U3.5
/USB_D-: J1.A7, J1.B7, U3.6
GND: C1.2, C2.2, C3.2, C4.2, C5.2, C6.2, C7.2, D1.1, D2.1, J1.A1, J1.A12, J1.B1, J1.B12, J1.SH, J2.16, J3.1, J3.16, J4.4, J5.1, R1.2, R2.2, SW1.1, SW2.1, U1.1, U1.15, U1.38, U1.39, U2.1, U3.1
unnamed: D1.2, R7.2
unnamed: D2.2, R8.2
unnamed: J1.A5, R1.1
unnamed: J1.B5, R2.1
unnamed: Q1.1, R3.2
unnamed: Q2.1, R4.2
